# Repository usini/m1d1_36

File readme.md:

µsini M1D1_36
-------------
An Open Source Midi controller with **36 pads** in a **compact body**.

Documentation en français : https://usini.github.io/m1d1_36/index.html

Make music on a PC or with open source sound modules.
* 36 capacitives pads  
* 4 Potentiometers    
* 10 buttons    

Based Sparkfun Pro Micro (atmega32u4)
https://www.sparkfun.com/products/12640

# Demo

# USB Midi
Compatible with any music software   
Can also be used as a keyboard / mouse / xbox360 controller...

## Examples
LMMS - Open Source Music Software - https://lmms.io/download#windows   

PatchBox OS - Raspberry Pi synthetiser - https://blokas.io/modep/

# Serial Midi
Add controls / sound generators using open sources modules

## Compatibles Modules
* **µsini zx** [TO BE PUBLISHED] : a AY-3-8910 sound generator (used in zx-spectrum)   
 Based on Ian Harvey design (public domain) : https://www.instructables.com/id/Arduino-MIDI-Chiptune-Synthesizer/

* **µsini opl2** [WAITING FOR COMPONENTS] : A OPL-2 FM sound generator (used in adlib sound card)   
  Based on Maarten Janssen design (MIT licence) : https://hackaday.io/project/18995-opl2-audio-board-for-arduino-raspberry-pi

* **µsini M1d1 Out** [TO MAKE] : A serial pins to Midi output
* **µsini M1d1 WiFi** [TO MAKE] : A serial midi to RtpMidi (WiFi Midi)
* **µsini M1d1 BLE** [TO MAKE] : A serial midi to BLE 

# Make your own
Fast and easy to solder as this midi controller used only modules.

## Send Gerbers to PCB Manufacturer

## Buy component
You can either choose to buy components from a chinese clone manufacturer or the original source.

### Clone links (sponsored)

### Sparkfun links

## Solder it

## Upload code

# Easy to customize code
Easy to use events system

Each times a pad / buttons is pressed or a potentiometers is moved, theses functions are triggered: 
* potsEvent()
* buttonsEvent()
* MPREvent()

Developer documentation : LINK

# Easy to customize schematics

noob friendly schematics for Kicad.  

## 3D models

* pro_micro.step - **Andrew_Witham** - https://grabcad.com/library/arduino-pro-micro-1
* stepdown.STEP - **Hasanain Shuja**   - https://grabcad.com/library/   dd0503ma-ultra-mini-dc-3-7v-4-5v-5v-to-3-3v-dc-dc-step-down-converter-buck-module-2    
* oled.step - **CDMX ELECTRONICA** - https://grabcad.com/library/display-oled-ssd1306-de-0-96-1     
* mpr121.step - **SPARKFUN** - https://www.sparkfun.com/products/retired/9695     
* logic_level.step - **SPARKFUN** - https://www.sparkfun.com/products/12009     
* 12mmx12mm Without cap.step - **Nilton** - https://grabcad.com/library/    
* 12mm-button-without-cap-with-round-square-cap-1
pot.step - **Mirko Ragni** - https://grabcad.com/library/47k-potentiometer-1   

# Open source as its core
## Make your own midi controller and sell it.   
Documentations / Codes and components, everything is licenced so you can make your own controller and sell it.

## Open source modules
Except for the OLED screen / 5v to 3.3v voltage regulator, all modules are licenced Creative Commons Share-alike 3.0 by Sparkfun.   

Eagles Files
* Pro Micro - http://cdn.sparkfun.com/datasheets/Dev/Arduino/Boards/SparkFun_Pro_Micro_v13a.zip

* MPR121 - http://cdn.sparkfun.com/datasheets/BreakoutBoards/MPR121-Breakout-v13.zip

* Logic Level Converter - http://cdn.sparkfun.com/datasheets/BreakoutBoards/Logic_Level_Bidirectional.zip

## Open Source code

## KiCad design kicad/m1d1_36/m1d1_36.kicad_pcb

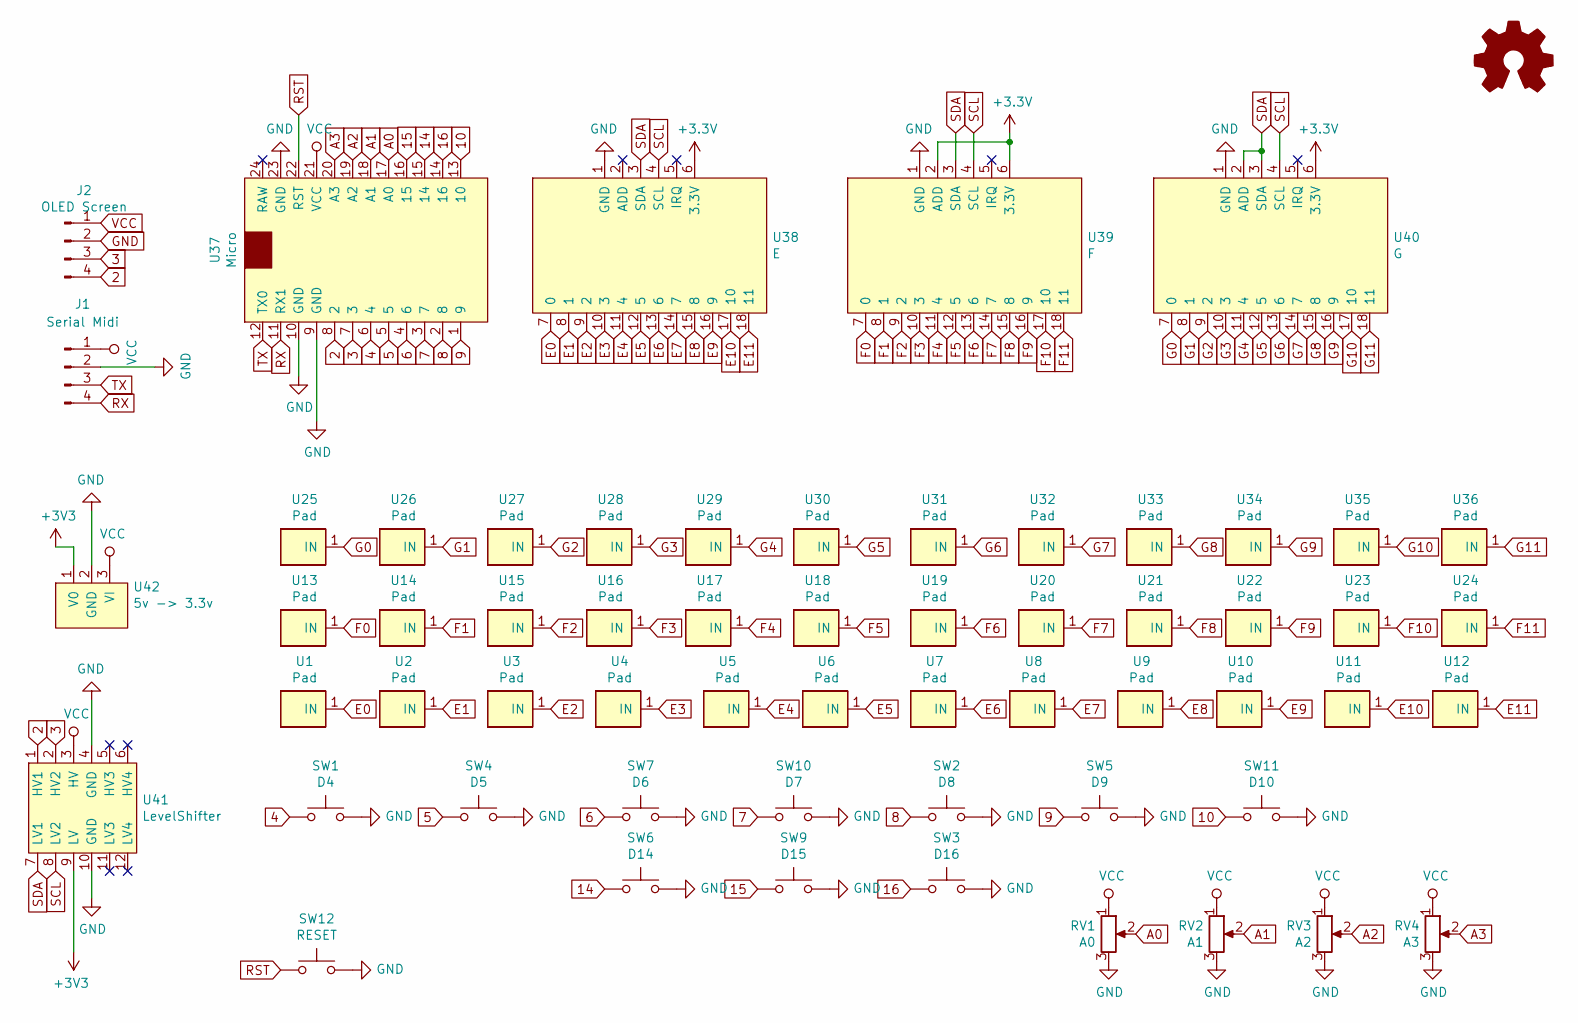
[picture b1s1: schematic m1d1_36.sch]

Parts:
J1: Serial Midi; PinHeader_1x04_P2.54mm_Horizontal
J2: OLED Screen; oled_128x64
RV1: A0; pot
RV2: A1; pot
RV3: A2; pot
RV4: A3; pot
SW1: D4; SW_PUSH-12mm
SW2: D8; SW_PUSH-12mm
SW3: D16; SW_PUSH-12mm
SW4: D5; SW_PUSH-12mm
SW5: D9; SW_PUSH-12mm
SW6: D14; SW_PUSH-12mm
SW7: D6; SW_PUSH-12mm
SW9: D15; SW_PUSH-12mm
SW10: D7; SW_PUSH-12mm
SW11: D10; SW_PUSH-12mm
SW12: RESET; SW_PUSH_6mm
U1, U2, U3, U4, U5, U6, U7, U8, U9, U10, U11, U12, U13, U14, U15, U16, U17, U18, U19, U20, U21, U22, U23, U24, U25, U26, U27, U28, U29, U30, U31, U32, U33, U34, U35, U36: Pad; pad
U37: Micro; pro_micro
U38: E; mpr121
U39: F; mpr121
U40: G; mpr121
U41: LevelShifter
U42: 5v -> 3.3v; voltage_regulator

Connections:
2: J2.4, U37.8 (2), U41.1 (HV1)
3: J2.3, U37.7 (3), U41.2 (HV2)
4: SW1.1, U37.6 (4)
5: SW4.1, U37.5
6: SW7.1, U37.4 (6)
7: SW10.1, U37.3 (7)
8: SW2.1, U37.2 (8)
9: SW5.1, U37.1 (9)
10: SW11.1, U37.13 (10)
14: SW6.1, U37.15 (14)
15: SW9.1, U37.16 (15)
16: SW3.1, U37.14 (16)
A0: RV1.2, U37.17 (A0)
A1: RV2.2, U37.18 (A1)
A2: RV3.2, U37.19 (A2)
A3: RV4.2, U37.20 (A3)
E0: U1.1, U38.7 (0)
E1: U2.1, U38.8 (1)
E2: U3.1, U38.9 (2)
E3: U4.1, U38.10 (3)
E4: U5.1, U38.11 (4)
E5: U6.1, U38.12 (5)
E6: U7.1, U38.13 (6)
E7: U8.1, U38.14 (7)
E8: U9.1, U38.15 (8)
E9: U10.1, U38.16 (9)
E10: U11.1, U38.17 (10)
E11: U12.1, U38.18 (11)
F0: U13.1, U39.7 (0)
F1: U14.1, U39.8 (1)
F2: U15.1, U39.9 (2)
F3: U16.1, U39.10 (3)
F4: U17.1, U39.11 (4)
F5: U18.1, U39.12 (5)
F6: U19.1, U39.13 (6)
F7: U20.1, U39.14 (7)
F8: U21.1, U39.15 (8)
F9: U22.1, U39.16 (9)
F10: U23.1, U39.17 (10)
F11: U24.1, U39.18 (11)
G0: U25.1, U40.7 (0)
G1: U26.1, U40.8 (1)
G2: U27.1, U40.9 (2)
G3: U28.1, U40.10 (3)
G4: U29.1, U40.11 (4)
G5: U30.1, U40.12 (5)
G6: U31.1, U40.13 (6)
G7: U32.1, U40.14 (7)
G8: U33.1, U40.15 (8)
G9: U34.1, U40.16 (9)
G10: U35.1, U40.17 (10)
G11: U36.1, U40.18 (11)
GND: J1.2, J2.2, RV1.3, RV2.3, RV3.3, RV4.3, SW1.2, SW2.2, SW3.2, SW4.2, SW5.2, SW6.2, SW7.2, SW9.2, SW10.2, SW11.2, SW12.2, U37.9 (GND), U37.10 (GND), U37.23 (GND), U38.1 (GND), U39.1 (GND), U40.1 (GND), U41.4 (GND), U41.10 (GND), U42.2 (GND)
RST: SW12.1, U37.22 (RST)
RX: J1.4, U37.11 (RX1)
SCL: U38.4 (SCL), U39.4 (SCL), U40.4 (SCL), U41.8 (LV2)
SDA: U38.3 (SDA), U39.3 (SDA), U40.2 (ADD), U40.3 (SDA), U41.7 (LV1)
TX: J1.3, U37.12 (TX0)
VCC: J1.1, J2.1, RV1.1, RV2.1, RV3.1, RV4.1, U37.21 (VCC), U41.3 (HV), U42.3 (VI)

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
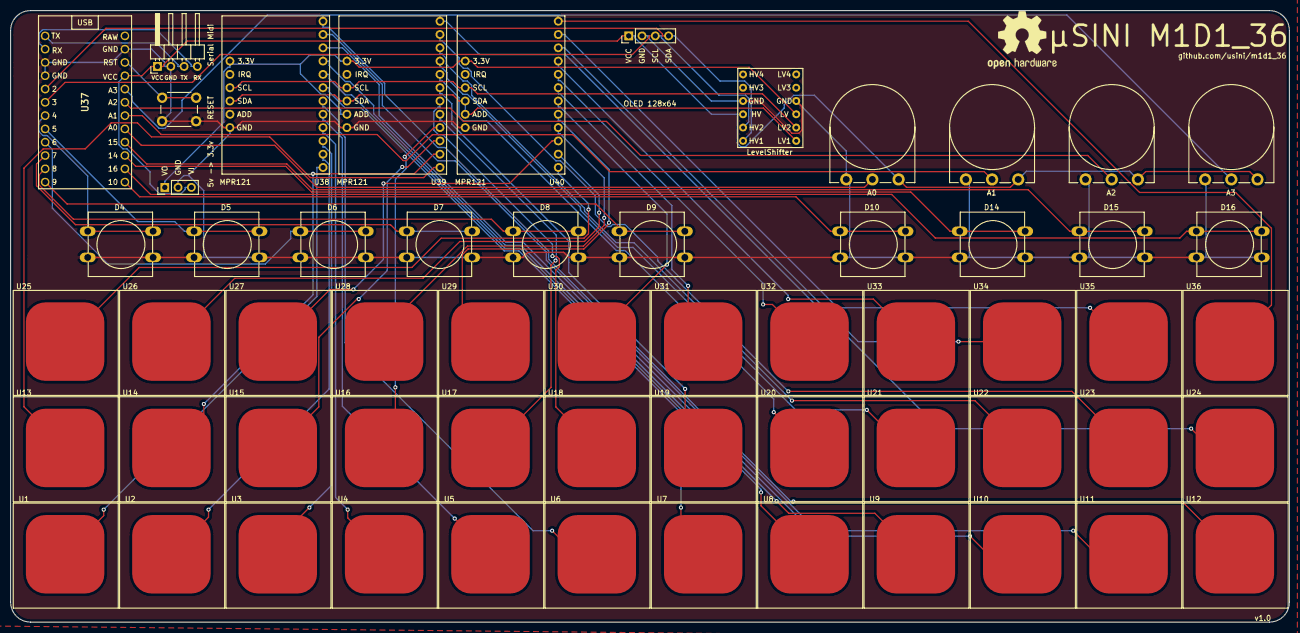
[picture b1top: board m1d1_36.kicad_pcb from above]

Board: 2 copper layers, 244.3 x 116.8 mm, 59 parts (0 on the bottom side), 60 nets.

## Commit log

2020-05-23 Dump v1.0
2020-05-23 Working on readme.md and photos
2020-05-25 rename doc to docs (for github pages)
2020-05-25 Change path to images in readme.md
2020-08-28 Add french doc (unfinished)
2021-02-24 Create branch docs / update documentation
2024-07-29 Add platformio project (just capacitive no buttons/pots)
